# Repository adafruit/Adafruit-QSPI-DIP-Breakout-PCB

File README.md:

## Adafruit QSPI DIP Breakout Board PCB

<a href="http://www.adafruit.com/products/5632"><br/>
Click here to purchase one from the Adafruit shop</a>

<a href="http://www.adafruit.com/products/5633"><br/>
Click here to purchase one from the Adafruit shop</a>

<a href="http://www.adafruit.com/products/5634"><br/>
Click here to purchase one from the Adafruit shop</a>

PCB files for the Adafruit QSPI DIP Breakout Board. 

Format is EagleCAD schematic and board layout
* https://www.adafruit.com/product/5632
* https://www.adafruit.com/product/5633
* https://www.adafruit.com/product/5634

### Description

For many modern and powerful chips like the RP2040, ESP32, RT10xx and STM32 series microcontrollers, designers can save money and reduce the number of chip options by not including building in the Flash memory used to store code and resources. Instead, an external QSPI Flash memory chip is wired up that can provide 16-128 Megabytes of memory (5632 - 16MB, 5633 - 64MB, 5634 - 128MB. It's not as fast as if it were on the microcontroller internal bus but with Quad SPI I/O and some clever caching by the chip designer, it's pretty effective!

To make prototyping and designing with QSPI flash a little easier, we designed these breakouts that convert the wide 8-SOIC packages to a cute 0.3" wide DIP. We find these handy when testing out different flash sizes, or if we just want to add more storage memory to a project.

This is the W25QXXJVSSIQ, a 3.3V power and logic chip. Note that the Q at the end means that the Quad Enable bit is permanently set in the status register. If you're using this in QSPI mode, then it'll work right out of the box. If you're using this in SPI mode, the 'hold' and 'write protect' pins don't do anything, so just connect them to 3.3V.

In Arduino, we have the Adafruit_SPIFlash library that can be used to interface with this chip - but don't forget it's only good for 3.3V logic and power! In CircuitPython, this chip has a TOML definition file so you could use it in a board definition.

Comes with a bit of header that can be used to solder in and plug into a breadboard or  to replace an existing socketted SPI flash DIP chip.

### License

Adafruit invests time and resources providing this open source design, please support Adafruit and open-source hardware by purchasing products from [Adafruit](https://www.adafruit.com)!

Designed by Limor Fried/Ladyada for Adafruit Industries.

Creative Commons Attribution/Share-Alike, all text above must be included in any redistribution. 
See license.txt for additional details.

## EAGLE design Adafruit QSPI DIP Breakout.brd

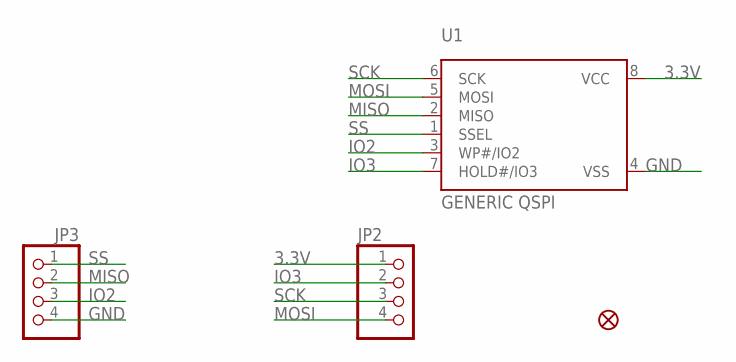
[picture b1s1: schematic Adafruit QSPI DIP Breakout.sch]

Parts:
FID1: FIDUCIAL_1MM
JP2, JP3: HEADER-1X476MIL; 1X04_ROUND_76
U1: GENERIC QSPI; SOIC8_208MIL

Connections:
3.3V: JP2.1, U1.8 (VCC)
GND: JP3.4, U1.4 (VSS)
IO2: JP3.3, U1.3 (WP#/IO2)
IO3: JP2.2, U1.7 (HOLD#/IO3)
MISO: JP3.2, U1.2 (MISO)
MOSI: JP2.4, U1.5 (MOSI)
SCK: JP2.3, U1.6 (SCK)
SS: JP3.1, U1.1 (SSEL)

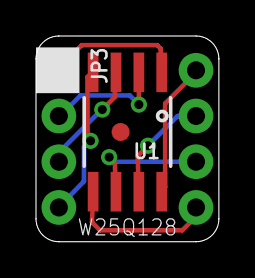
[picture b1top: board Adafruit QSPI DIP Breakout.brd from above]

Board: 2 copper layers, 10.2 x 11.4 mm, 5 parts (1 on the bottom side), 8 nets.

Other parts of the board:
U$4: ADAFRUIT_2.5MM

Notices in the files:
parts and their libraries:
microbuilder: This work is placed in the public domain, and may be freely used for commercial and non-commercial work with the following conditions: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
